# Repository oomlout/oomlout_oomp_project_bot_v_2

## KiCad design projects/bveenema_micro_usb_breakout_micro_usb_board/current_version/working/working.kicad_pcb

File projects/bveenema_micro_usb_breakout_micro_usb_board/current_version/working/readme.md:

# micro_usb_breakout
 
## summary 
* id: bveenema_micro_usb_breakout_micro_usb_board
* user: bveenema
* name: micro_usb_breakout
* board: micro_usb_board
* repo: https://github.com/bveenema/Micro-USB-Breakout
* src_file_repo_kicad_pcb: Obsolete/Rev A/Micro-USB-Board.kicad_pcb
* src_file_repo_kicad_pcb_link: https://github.com/bveenema/Micro-USB-Breakout/tree/master/Obsolete/Rev A/Micro-USB-Board.kicad_pcb

* src_file_repo_sch: Obsolete/Rev A/Micro-USB-Board.sch
* src_file_repo_sch_link: https://github.com/bveenema/Micro-USB-Breakout/tree/master/Obsolete/Rev A/Micro-USB-Board.sch
* full details link: https://github.com/oomlout/oomlout_oomp_project_bot_v_2/tree/main/projects/bveenema_micro_usb_breakout_micro_usb_board/current_version/working

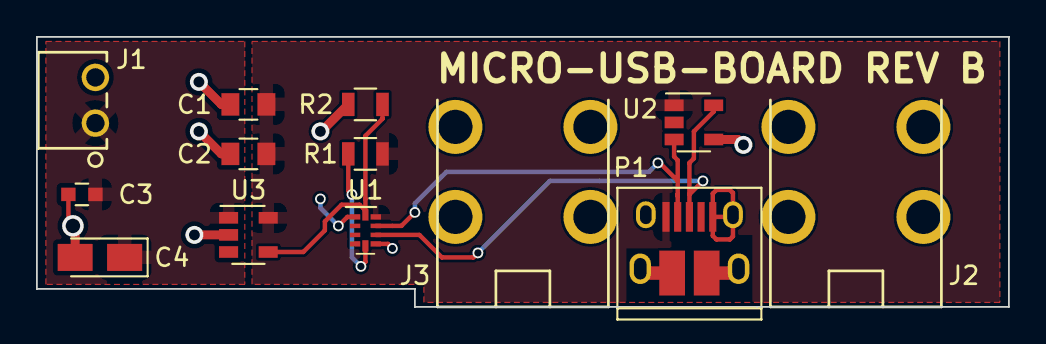
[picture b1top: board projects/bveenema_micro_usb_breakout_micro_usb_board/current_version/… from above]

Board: 2 copper layers, 54.0 x 15.0 mm, 13 parts (0 on the bottom side), 7 nets.

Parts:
C1: 10uF; C_0805
C2: 1uF; C_0805
C3: .1uF; C_0603
C4: 100uF; CP_Tantalum_Case-A_EIA-3216-18_Reflow
J1: 640455-2
J2, J3: Keystone-7790; 7790-ScrewTerm-M3
P1: USB_OTG; USB_Micro-B_10103594-0001LF
R1, R2: 100K; R_0805
U1: BQ24392; Texas_R_PUQFN-N10
U2: TPD2E001; SOT-23-5
U3: AP22811A; SOT-23-5

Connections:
+5V: C3.2, C4.1, J1.1, U3.1
/CHG_DET: R2.1, U1.10, U3.4
/VBUS: C1.2, C2.1, P1.1, R1.1, U1.9, U2.1, U3.5
GND: C1.1, C2.2, C3.1, C4.2, J1.2, P1.5, P1.6, R2.2, U1.6, U2.4, U3.2
unnamed: P1.2, U1.8, U2.3
unnamed: P1.3, U1.7, U2.5
unnamed: R1.2, U1.5

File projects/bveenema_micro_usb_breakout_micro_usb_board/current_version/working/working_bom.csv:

"Id";"Designator";"Footprint";"Quantity";"Designation";"Supplier and ref";
1;"C1";"C_0805";1;"10uF";;;
2;"C2";"C_0805";1;"1uF";;;
3;"C3";"C_0603";1;".1uF";;;
4;"C4";"CP_Tantalum_Case-A_EIA-3216-18_Reflow";1;"100uF";;;
5;"J1";"640455-2";1;"640455-2";;;
6;"P1";"USB_Micro-B_10103594-0001LF";1;"USB_OTG";;;
7;"R1,R2";"R_0805";2;"100K";;;
8;"U1";"Texas_R_PUQFN-N10";1;"BQ24392";;;
9;"U2";"SOT-23-5";1;"TPD2E001";;;
10;"U3";"SOT-23-5";1;"AP22811A";;;
11;"J2,J3";"7790-ScrewTerm-M3";2;"Keystone-7790";;;

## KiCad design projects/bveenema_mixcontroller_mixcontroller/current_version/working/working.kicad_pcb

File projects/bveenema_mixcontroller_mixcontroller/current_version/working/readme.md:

# mixcontroller
 
## summary 
* id: bveenema_mixcontroller_mixcontroller
* user: bveenema
* name: mixcontroller
* board: mixcontroller
* repo: https://github.com/bveenema/MixController
* src_file_repo_kicad_pcb: PCB/MixController.kicad_pcb
* src_file_repo_kicad_pcb_link: https://github.com/bveenema/MixController/tree/master/PCB/MixController.kicad_pcb

* src_file_repo_sch: PCB/MixController.sch
* src_file_repo_sch_link: https://github.com/bveenema/MixController/tree/master/PCB/MixController.sch
* full details link: https://github.com/oomlout/oomlout_oomp_project_bot_v_2/tree/main/projects/bveenema_mixcontroller_mixcontroller/current_version/working

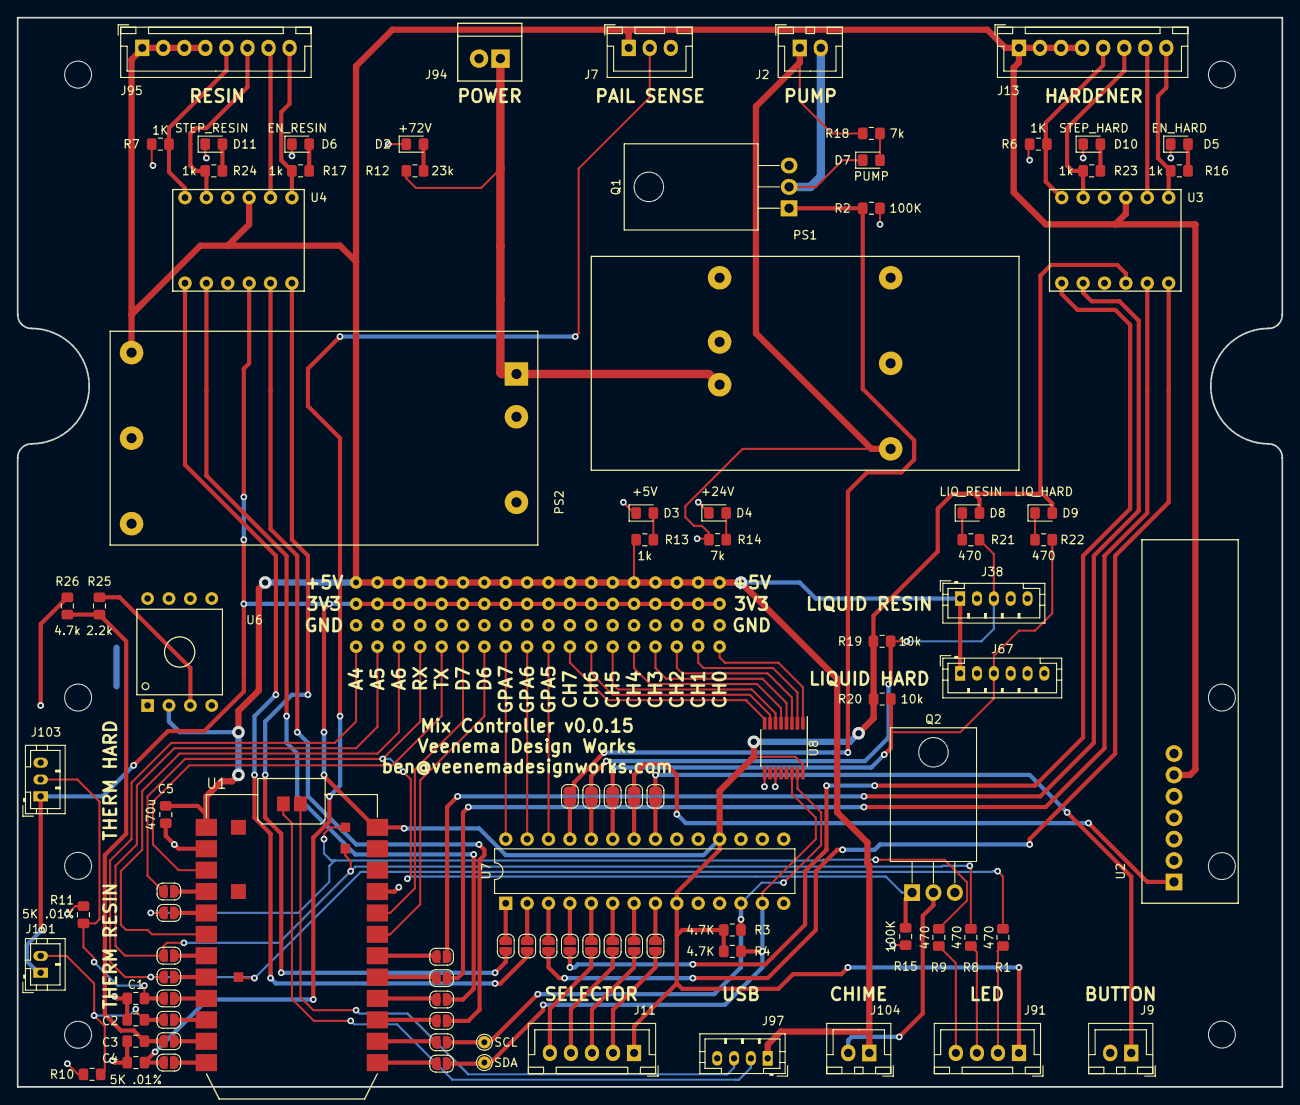
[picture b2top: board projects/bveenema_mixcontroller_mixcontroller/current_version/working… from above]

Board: 2 copper layers, 150.2 x 127.0 mm, 166 parts (0 on the bottom side), 100 nets.

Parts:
C1, C2, C3, C4: 0.1u; C_0805_2012Metric_Pad1.15x1.40mm_HandSolder
C5: 470u; C_0805_2012Metric_Pad1.15x1.40mm_HandSolder
D2: +72V; LED_0805_2012Metric_Pad1.15x1.40mm_HandSolder
D3: +5V; LED_0805_2012Metric_Pad1.15x1.40mm_HandSolder
D4: +24V; LED_0805_2012Metric_Pad1.15x1.40mm_HandSolder
D5: EN_HARD; LED_0805_2012Metric_Pad1.15x1.40mm_HandSolder
D6: EN_RESIN; LED_0805_2012Metric_Pad1.15x1.40mm_HandSolder
D7: PUMP; LED_0805_2012Metric_Pad1.15x1.40mm_HandSolder
D8: LIQ_RESIN; LED_0805_2012Metric_Pad1.15x1.40mm_HandSolder
D9: LIQ_HARD; LED_0805_2012Metric_Pad1.15x1.40mm_HandSolder
D10: STEP_HARD; LED_0805_2012Metric_Pad1.15x1.40mm_HandSolder
D11: STEP_RESIN; LED_0805_2012Metric_Pad1.15x1.40mm_HandSolder
J2, J9, J104: B2B-XH-A(LF)(SN); JST_XH_B02B-XH-A_1x02_P2.50mm_Vertical
J7: B3B-XH-A(LF)(SN); JST_XH_B03B-XH-A_1x03_P2.50mm_Vertical
J11: B5B-XH-A(LF)(SN); JST_XH_B05B-XH-A_1x05_P2.50mm_Vertical
J13, J95: B8B-XH-A(LF)(SN); JST_XH_B08B-XH-A_1x08_P2.50mm_Vertical
J15, J16, J17, J18, J19, J20, J21, J22, J23, J24, J25, J26, J27, J28, J29, J30, J31, J32, J33, J34, J35, J36, J37, J39, J40, J41, J42, J43, J44, J45, J46, J47, J48, J49, J50, J51, J52, J53, J54, J56, J57, J58, J59, J60, J61, J62, J63, J64, J65, J66, J68, J69, J70, J72, J73, J74, J75, J76, J77, J78, J79, J80, J81, J82, J83, J84, J85, J86, J87, J88, J89, J90: ConnectorPoint_THT_D1.5mm_Drill-0.7mm
J38: B5B-PH-K-S(LF)(SN); JST_PH_B5B-PH-K_1x05_P2.00mm_Vertical
J67: B6B-PH-K-S(LF)(SN); JST_PH_B6B-PH-K_1x06_P2.00mm_Vertical
J91: B4B-XH-A(LF)(SN); JST_XH_B04B-XH-A_1x04_P2.50mm_Vertical
J94: 0705430001; Molex-705430001_02x2.54mm_Straight
J97: B4B-PH-K-S(LF)(SN); JST_PH_B4B-PH-K_1x04_P2.00mm_Vertical
J101: B2B-PH-K-S(LF)(SN); JST_PH_B2B-PH-K_1x02_P2.00mm_Vertical
J103: B3B-PH-K-S(LF)(SN); JST_PH_B3B-PH-K_1x03_P2.00mm_Vertical
JP1, JP2, JP3, JP4, JP5, JP6, JP7, JP8, JP9, JP10, JP11, JP12, JP13, JP14, JP15, JP16, JP17, JP18, JP19, JP20, JP21, JP22, JP23, JP24, JP25, JP26, JP27: SolderJumper-2_P1.3mm_Open_RoundedPad1.0x1.5mm
PS1: ERM01H110
PS2: RSDW20H-05; RSDW20_H
Q1, Q2: Q_NMOS_GDS; TO-220-3_Horizontal_TabDown
R1, R8, R9, R21, R22: 470; R_0805_2012Metric_Pad1.15x1.40mm_HandSolder
R2, R15: 100K; R_0805_2012Metric_Pad1.15x1.40mm_HandSolder
R3, R4: 4.7K; R_0805_2012Metric_Pad1.15x1.40mm_HandSolder
R6, R7: 1K; R_0805_2012Metric_Pad1.15x1.40mm_HandSolder
R10, R11: 5K .01%; R_0805_2012Metric_Pad1.15x1.40mm_HandSolder
R12: 23k; R_0805_2012Metric_Pad1.15x1.40mm_HandSolder
R13, R16, R17, R23, R24: 1k; R_0805_2012Metric_Pad1.15x1.40mm_HandSolder
R14, R18: 7k; R_0805_2012Metric_Pad1.15x1.40mm_HandSolder
R19, R20: 10k; R_0805_2012Metric_Pad1.15x1.40mm_HandSolder
R25: 2.2k; R_0805_2012Metric_Pad1.15x1.40mm_HandSolder
R26: 4.7k; R_0805_2012Metric_Pad1.15x1.40mm_HandSolder
TP1: SCL; TestPoint_THTPad_D1.5mm_Drill0.7mm
TP2: SDA; TestPoint_THTPad_D1.5mm_Drill0.7mm
U1: Photon; photon_smd
U2: Adafruit_1096; SimpleRF_Receiver
U3, U4: BOB-12009; BOB-12_W10.16mm
U6: HSCDANN005PGAA5; HoneyWell_DIP_AN
U7: MCP23017_SP; DIP-28_W7.62mm
U8: ADS7830; TSSOP-16_4.4x5mm_P0.65mm

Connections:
+3V3: D8.2, D9.2, J11.1, J20.1, J21.1, J22.1, J23.1, J24.1, J47.1, J48.1, J49.1, J50.1, J51.1, J52.1, J53.1, J54.1, J56.1, J57.1, J58.1, J87.1, J88.1, J91.1, J101.1, J103.1, R3.1, R4.1, R19.1, R20.1, U1.24, U3.4, U4.4, U7.9, U7.18, U8.16
+5V: C5.2, J7.1, J13.1, J13.2, J13.3, J13.4, J15.1, J16.1, J17.1, J18.1, J19.1, J30.1, J31.1, J32.1, J33.1, J34.1, J35.1, J36.1, J37.1, J38.1, J39.1, J40.1, J41.1, J67.1, J89.1, J90.1, J95.1, J95.2, J95.3, J95.4, J97.1, J104.1, PS2.3, R13.1, U1.1, U2.6, U3.9, U4.9, U6.2
+24V: J2.1, PS1.4, R14.2, R18.2
+72V: J94.1, PS1.1, PS2.1, R12.2
/CHIME: J43.1, JP26.1, Q2.1, R15.1
/HARDENER_ENABLE: JP8.1, U3.6
/HARDENER_HLFB: JP9.1, U3.1
/HARDENER_INPUT_DIR: JP19.2, U3.5
/HARDENER_INPUT_STEP: JP18.2, U3.2
/LIQUID_SNS_HARDENER: J67.3, JP16.1, R20.2, R22.1
/LIQUID_SNS_RESIN: J38.3, JP17.1, R19.2, R21.1
/PAIL_SNS: C4.2, J7.2, JP5.1
/PRESS_SNS: C3.2, JP4.1, R25.2, R26.1
/PUMP_EN: JP27.1, Q1.1, R2.1
/RESIN_ENABLE: JP6.1, U4.6
/RESIN_HLFB: JP7.1, U4.1
/RESIN_INPUT_DIR: JP21.2, U4.5
/RESIN_INPUT_STEP: JP20.2, U4.2
/ROTARY_1: J11.2, JP13.1
/ROTARY_2: J11.3, JP12.1
/ROTARY_3: J11.4, JP11.1
/ROTARY_4: J11.5, JP10.1
/SCL: JP22.2, R3.2, TP1.1, U7.12, U8.15
/SDA: JP23.2, R4.2, TP2.1, U7.13, U8.14
/STATUS_LED_B: JP1.1, R9.1, U1.29
/STATUS_LED_G: J45.1, JP2.1, R8.1, U1.28
/STATUS_LED_R: J46.1, JP3.1, R1.1, U1.27
/THERM_HARDENER: C1.2, J103.2, JP24.1, R11.1
/THERM_RESIN: C2.2, J101.2, JP25.1, R10.1
/USB(+): J97.2, U1.31
/USB(-): J97.3, U1.30
/USER_BUTTON: J9.1, JP14.1
/USER_REMOTE: JP15.1, U2.1
GND: C1.1, C2.1, C3.1, C4.1, C5.1, D2.1, D3.1, D4.1, D5.1, D6.1, D10.1, D11.1, J7.3, J9.2, J25.1, J26.1, J27.1, J28.1, J29.1, J38.2, J38.4, J59.1, J60.1, J61.1, J62.1, J63.1, J64.1, J65.1, J66.1, J67.2, J67.4, J68.1, J69.1, J70.1, J85.1, J86.1, J94.2, J97.4, PS1.2, PS1.6, PS2.2, PS2.5, Q1.3, Q2.3, R2.2, R6.1, R7.1, R10.2, R11.2, R15.2, R26.2, U1.2, U1.21, U2.7, U3.3, U3.10, U4.3, U4.10, U6.4, U7.10, U8.9, U8.11
unnamed: D2.2, R12.1
unnamed: D3.2, R13.2
unnamed: D4.2, R14.1
unnamed: D5.2, R16.2
unnamed: D6.2, R17.2
unnamed: D7.1, J2.2, Q1.2
unnamed: D7.2, R18.1
unnamed: D8.1, R21.2
unnamed: D9.1, R22.2
unnamed: D10.2, R23.2
unnamed: D11.2, R24.2
unnamed: J13.5, R6.2, U3.12
unnamed: J13.6, R23.1, U3.11
unnamed: J13.7, U3.8
unnamed: J13.8, R16.1, U3.7
unnamed: J42.1, U1.3
unnamed: J44.1, U1.6
unnamed: J72.1, U7.26
unnamed: J73.1, U7.27
unnamed: J74.1, U7.28
unnamed: J75.1, U8.1
unnamed: J76.1, U8.2
unnamed: J77.1, U8.3
unnamed: J78.1, U8.4
unnamed: J79.1, U8.5
unnamed: J80.1, U8.6
unnamed: J81.1, U8.7
unnamed: J82.1, U8.8
unnamed: J83.1, U1.20
unnamed: J84.1, U1.19
unnamed: J91.2, R1.2
unnamed: J91.3, R8.2
unnamed: J91.4, R9.2
unnamed: J95.5, R7.2, U4.12
unnamed: J95.6, R24.1, U4.11
unnamed: J95.7, U4.8
unnamed: J95.8, R17.1, U4.7
unnamed: J104.2, Q2.2
unnamed: JP1.2, U1.5
unnamed: JP2.2, U1.7
unnamed: JP3.2, U1.8
unnamed: JP4.2, U1.11
unnamed: JP5.2, U1.12
unnamed: JP6.2, U7.1
unnamed: JP7.2, U7.2
unnamed: JP8.2, U7.3
unnamed: JP9.2, U7.4
unnamed: JP10.2, U7.5
unnamed: JP11.2, U7.6
unnamed: JP12.2, U7.7
unnamed: JP13.2, U7.8
unnamed: JP14.2, U7.21
unnamed: JP15.2, U7.22
unnamed: JP16.2, U7.23
unnamed: JP17.2, U7.24
unnamed: JP18.1, U1.18
unnamed: JP19.1, U1.17
unnamed: JP20.1, U1.16
unnamed: JP21.1, U1.15
unnamed: JP22.1, U1.14
unnamed: JP23.1, U1.13
unnamed: JP24.2, U1.9
unnamed: JP25.2, U1.10
unnamed: JP26.2, U1.4
unnamed: JP27.2, U7.25
unnamed: R25.1, U6.3

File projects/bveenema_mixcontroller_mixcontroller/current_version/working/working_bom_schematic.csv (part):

"Source:","C:\gh\oomlout_oomp_project_bot_v_2\projects\bveenema_mixcontroller_mixcontroller\current_version\working\working.kicad_sch"
"Date:","27/09/2023 21:59:41"
"Tool:","Eeschema 7.0.6"
"Generator:","C:/Program Files/KiCad/7.0/bin/scripting/plugins/bom_csv_grouped_by_value_with_fp.py"
"Component Count:","216"
"Ref","Qnty","Value","Cmp name","Footprint","Description","Vendor","DNP"
"C1, C2, C3, C4","4","0.1u","C_Small","Capacitor_SMD:C_0805_2012Metric_Pad1.15x1.40mm_HandSolder","Unpolarized capacitor, small symbol","DigiKey",""
"C5","1","47u","C_Small","Capacitor_SMD:C_0805_2012Metric_Pad1.15x1.40mm_HandSolder","Unpolarized capacitor, small symbol","DigiKey",""
"D1","1","LED_ARGB","LED_ARGB","NoFootprint:NoFootprint","RGB LED, anode/red/green/blue","DigiKey",""
"D2","1","+72V","LED_ALT-Device","LED_SMD:LED_0805_2012Metric_Pad1.15x1.40mm_HandSolder","","DigiKey",""
"D3","1","+5V","LED_ALT-Device","LED_SMD:LED_0805_2012Metric_Pad1.15x1.40mm_HandSolder","","DigiKey",""
"D4","1","+24V","LED_ALT-Device","LED_SMD:LED_0805_2012Metric_Pad1.15x1.40mm_HandSolder","","DigiKey",""
"D5","1","EN_HARD","LED_ALT-Device","LED_SMD:LED_0805_2012Metric_Pad1.15x1.40mm_HandSolder","","DigiKey",""
"D6","1","EN_RESIN","LED_ALT-Device","LED_SMD:LED_0805_2012Metric_Pad1.15x1.40mm_HandSolder","","DigiKey",""
"D7","1","PUMP","LED_ALT-Device","LED_SMD:LED_0805_2012Metric_Pad1.15x1.40mm_HandSolder","","DigiKey",""
"D8","1","LIQ_RESIN","LED_ALT-Device","LED_SMD:LED_0805_2012Metric_Pad1.15x1.40mm_HandSolder","","DigiKey",""
"D9","1","LIQ_HARD","LED_ALT-Device","LED_SMD:LED_0805_2012Metric_Pad1.15x1.40mm_HandSolder","","DigiKey",""
"D10","1","STEP_HARD","LED_ALT-Device","LED_SMD:LED_0805_2012Metric_Pad1.15x1.40mm_HandSolder","","DigiKey",""
"D11","1","STEP_RESIN","LED_ALT-Device","LED_SMD:LED_0805_2012Metric_Pad1.15x1.40mm_HandSolder","","DigiKey",""
"D12","1","LED_RESIN_LIQ","LED_ALT-Device","NoFootprint:NoFootprint","","DigiKey",""
"D13","1","LED_HARD_LIQ","LED_ALT-Device","NoFootprint:NoFootprint","","DigiKey",""
"J1, J5, J6","3","PG7","Conn_01x02_Female-Connector","NoFootprint:NoFootprint","","Amazon",""
"J2, J9, J104","3","B2B-XH-A(LF)(SN)","Conn_01x02_Male-Connector","Connector_JST:JST_XH_B02B-XH-A_1x02_P2.50mm_Vertical","","DigiKey",""
"J3, J10, J105","3","XHP-2","Conn_01x02_Female-Connector","NoFootprint:NoFootprint","","DigiKey",""
"J4, J8","2","XHP-3","Conn_01x03_Female-Connector","NoFootprint:NoFootprint","","DigiKey",""
"J7","1","B3B-XH-A(LF)(SN)","Conn_01x03_Male-Connector","Connector_JST:JST_XH_B03B-XH-A_1x03_P2.50mm_Vertical","","DigiKey",""
"J11","1","B5B-XH-A(LF)(SN)","Conn_01x05_Male-Connector","Connector_JST:JST_XH_B05B-XH-A_1x05_P2.50mm_Vertical","","DigiKey",""
"J12","1","XHP-5","Conn_01x05_Female-Connector","NoFootprint:NoFootprint","","DigiKey",""
"J13, J95","2","B8B-XH-A(LF)(SN)","Conn_01x08_Male-Connector","Connector_JST:JST_XH_B08B-XH-A_1x08_P2.50mm_Vertical","","DigiKey",""
"J14, J96","2","XHP-8","Conn_01x08_Female-Connector","NoFootprint:NoFootprint","","DigiKey",""
"J15, J16, J17, J18, J19, J20, J21, J22, J23, J24, J25, J26, J27, J28, J29, J30, J31, J32, J33, J34, J35, J36, J37, J39, J40, J41, J42, J43, J44, J45, J46, J47, J48, J49, J50, J51, J52, J53, J54, J56, J57, J58, J59, J60, J61, J62, J63, J64, J65, J66, J68, J69, J70, J72, J73, J74, J75, J76, J77, J78, J79, J80, J81, J82, J83, J84, J85, J86, J87, J88, J89, J90","72","~","TestPoint","Local:ConnectorPoint_THT_D1.5mm_Drill-0.7mm","test point","",""
"J38","1","B5B-PH-K-S(LF)(SN)","Conn_01x05_Male-Connector","Connector_JST:JST_PH_B5B-PH-K_1x05_P2.00mm_Vertical","","DigiKey",""
"J55","1","PHR-5","Conn_01x05_Female-Connector","NoFootprint:NoFootprint","","DigiKey",""
"J67","1","B6B-PH-K-S(LF)(SN)","Conn_01x06_Male-Connector","Connector_JST:JST_PH_B6B-PH-K_1x06_P2.00mm_Vertical","","DigiKey",""
"J71","1","PHR-6","Conn_01x06_Female-Connector","NoFootprint:NoFootprint","","DigiKey",""
"J91","1","B4B-XH-A(LF)(SN)","Conn_01x04_Male-Connector","Connector_JST:JST_XH_B04B-XH-A_1x04_P2.50mm_Vertical","","DigiKey",""
"J92","1","XHP-4","Conn_01x04_Female-Connector","NoFootprint:NoFootprint","","DigiKey",""
"J93","1","50-57-9402","Conn_01x02_Female-Connector","NoFootprint:NoFootprint","","DigiKey",""
"J94","1","0705430001","Conn_01x02_Male-Connector","VDW-Connectors:Molex-705430001_02x2.54mm_Straight","","DigiKey",""
"J97","1","B4B-PH-K-S(LF)(SN)","Conn_01x04_Male-Connector","Connector_JST:JST_PH_B4B-PH-K_1x04_P2.00mm_Vertical","","DigiKey",""
"J98","1","PHR-4","Conn_01x04_Female-Connector","NoFootprint:NoFootprint","","DigiKey",""
"J99","1","USB_B","USB_B-Connector","NoFootprint:NoFootprint","","DigiKey",""
"J100","1","PHR-2","Conn_01x02_Female-Connector","NoFootprint:NoFootprint","","DigiKey",""
"J101","1","B2B-PH-K-S(LF)(SN)","Conn_01x02_Male-Connector","Connector_JST:JST_PH_B2B-PH-K_1x02_P2.00mm_Vertical","","DigiKey",""
"J102","1","PHR-3","Conn_01x03_Female-Connector","NoFootprint:NoFootprint","","DigiKey",""
"J103","1","B3B-PH-K-S(LF)(SN)","Conn_01x03_Male-Connector","Connector_JST:JST_PH_B3B-PH-K_1x03_P2.00mm_Vertical","","DigiKey",""
"J106, J108","2","JST SM Male","Conn_01x02_Male-Connector","NoFootprint:NoFootprint","","DigiKey",""
"J107, J109","2","JST SM Female","Conn_01x02_Female-Connector","NoFootprint:NoFootprint","","DigiKey",""
"JP1, JP2, JP3, JP4, JP5, JP6, JP7, JP8, JP9, JP10, JP11, JP12, JP13, JP14, JP15, JP16, JP17, JP18, JP19, JP20, JP21, JP22, JP23, JP24, JP25, JP26, JP27","27","~","Jumper_NC_Small-Device","Jumper:SolderJumper-2_P1.3mm_Open_RoundedPad1.0x1.5mm","","",""
"K1","1","G2R-1A-T DC48","DIPxx-1Axx-11x","NoFootprint:NoFootprint","Standex Meder DIP reed relay, SPST, Closing Contact","DigiKey",""
"KB1","1","Knob","Knob-VDW_Mechanical","NoFootprint:NoFootprint","","DigiKey",""
"LS1","1","Speaker","Speaker","NoFootprint:NoFootprint","Speaker","DigiKey",""
"PS1","1","ERM01H110","ERM01H110-VDW_Modules","VDW-Modules:ERM01H110","","Mouser",""
"PS2","1","RSDW20H-05","RSDW20H-05-VDW_Modules","VDW-Modules:RSDW20_H","","Mouser",""
"Q1, Q2","2","Q_NMOS_GDS","Q_NMOS_GDS","Package_TO_SOT_THT:TO-220-3_Horizontal_TabDown","N-MOSFET transistor, gate/drain/source","DigiKey",""
"R1, R8, R9, R21, R22","5","470","R_Small","Resistor_SMD:R_0805_2012Metric_Pad1.15x1.40mm_HandSolder","Resistor, small symbol","DigiKey",""
"R2, R15","2","100k","R_Small","Resistor_SMD:R_0805_2012Metric_Pad1.15x1.40mm_HandSolder","Resistor, small symbol","DigiKey",""
"R3, R4, R26","3","4.7k","R_Small","Resistor_SMD:R_0805_2012Metric_Pad1.15x1.40mm_HandSolder","Resistor, small symbol","DigiKey",""
"R5","1","2.2k","R","NoFootprint:NoFootprint","Resistor","House",""
"R6, R7, R13, R16, R17, R23, R24","7","1k","R_Small","Resistor_SMD:R_0805_2012Metric_Pad1.15x1.40mm_HandSolder","Resistor, small symbol","DigiKey",""
"R10, R11","2","4.99k .1%","R_Small","Resistor_SMD:R_0805_2012Metric_Pad1.15x1.40mm_HandSolder","Resistor, small symbol","DigiKey",""
"R12","1","22k","R_Small","Resistor_SMD:R_0805_2012Metric_Pad1.15x1.40mm_HandSolder","Resistor, small symbol","DigiKey",""
"R14, R18","2","7.5k","R_Small","Resistor_SMD:R_0805_2012Metric_Pad1.15x1.40mm_HandSolder","Resistor, small symbol","DigiKey",""
"R19, R20","2","10k","R_Small","Resistor_SMD:R_0805_2012Metric_Pad1.15x1.40mm_HandSolder","Resistor, small symbol","DigiKey",""
"R25","1","2.2k","R_Small","Resistor_SMD:R_0805_2012Metric_Pad1.15x1.40mm_HandSolder","Resistor, small symbol","DigiKey",""
"R27, R28","2","470","R_Small","NoFootprint:NoFootprint","Resistor, small symbol","House",""
"R29","1","22k","R","NoFootprint:NoFootprint","Resistor","House",""
"SP1, SP8, SP9","3","LED_HOLDER_5MM","LED_HOLDER_5MM-VDW_Mechanical","NoFootprint:NoFootprint","","DigiKey",""
"SP2, SP3, SP4, SP5, SP6, SP7","6","PG7","PG7-VDW_Mechanical","NoFootprint:NoFootprint","","Amazon",""
"SW1","1","Rotary_Selector_Switch","Rotary_Selector_Switch-VDW_Modules","NoFootprint:NoFootprint","","DigiKey",""
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
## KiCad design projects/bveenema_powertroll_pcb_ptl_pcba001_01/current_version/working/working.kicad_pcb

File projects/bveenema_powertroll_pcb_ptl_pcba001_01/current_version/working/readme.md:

# powertroll_pcb
 
## summary 
* id: bveenema_powertroll_pcb_ptl_pcba001_01
* user: bveenema
* name: powertroll_pcb
* board: ptl_pcba001_01
* repo: https://github.com/bveenema/powertroll-pcb
* src_file_repo_kicad_pcb: PTL-PCBA001-01.kicad_pcb
* src_file_repo_kicad_pcb_link: https://github.com/bveenema/powertroll-pcb/tree/master/PTL-PCBA001-01.kicad_pcb

* src_file_repo_sch: PTL-PCBA001-01.sch
* src_file_repo_sch_link: https://github.com/bveenema/powertroll-pcb/tree/master/PTL-PCBA001-01.sch
* full details link: https://github.com/oomlout/oomlout_oomp_project_bot_v_2/tree/main/projects/bveenema_powertroll_pcb_ptl_pcba001_01/current_version/working

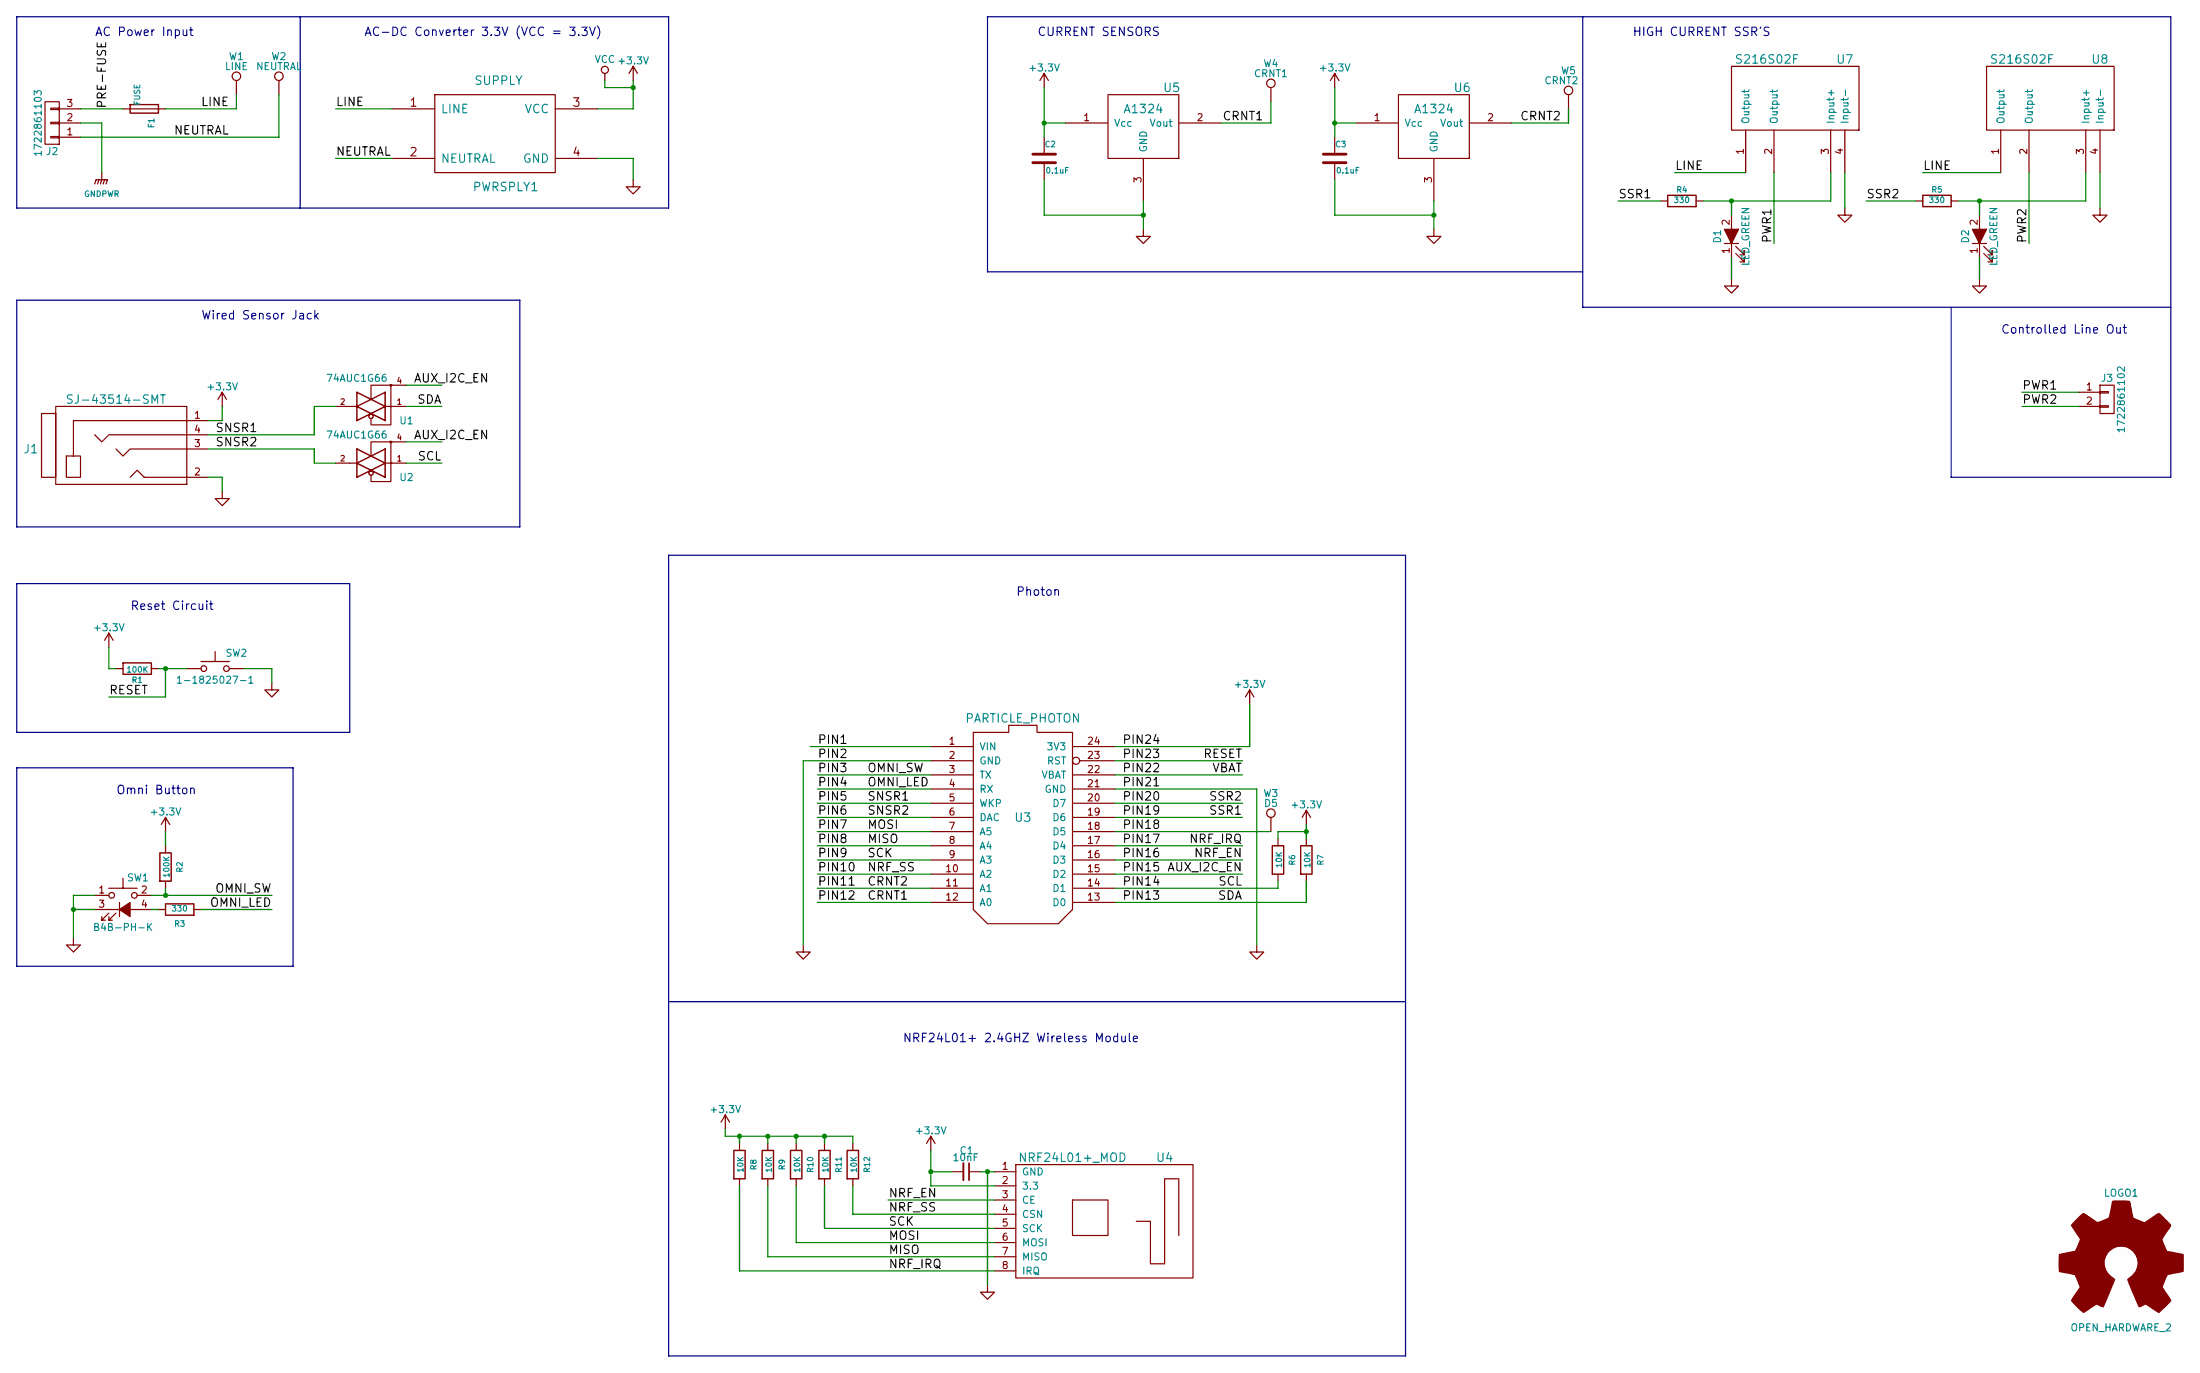
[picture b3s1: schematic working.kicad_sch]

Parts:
C1: 10nF; C_0805; Part Number CL21B103KBANNNC
C2, C3: 0.1uF; C_0805_HandSoldering
D1, D2: LED_GREEN; LED_0805
F1: FUSE; Fuseholder5x20_horiz_open_inline_Type-I
J1: SJ-43514-SMT
J2: 1722861103; Molex_UltraFit-1722861103_3x3.50mm_Straight
J3: 1722861102; Molex_UltraFit-1722861102_2x3.50mm_Straight
LOGO1: OPEN_HARDWARE_2; OSHW-Symbol_6.7x6mm_SilkScreen
PWRSPLY1: SUPPLY; PowerSupply
R1, R2: 100K; R_0805_HandSoldering
R3, R4, R5: 330; R_0805_HandSoldering
R6, R7, R8, R9, R10, R11, R12: 10K; R_0805_HandSoldering
SW1: B4B-PH-K; JST_PH_B4B-PH-K_04x2.00mm_Straight
SW2: 1-1825027-1; SW_Tactile_SPST_Angled
U1, U2: 74AUC1G66; SOT-23-5
U3: PARTICLE_PHOTON; photon
U4: NRF24L01+_MOD; NRF24L01
U5, U6: A1324; SOT-23
U7, U8: S216S02F; S216S02
W1: LINE; Measurement_Point_Round-TH_Small
W2: NEUTRAL; Measurement_Point_Round-TH_Small
W3: D5; Measurement_Point_Round-TH_Small
W4: CRNT1; Measurement_Point_Round-SMD-Pad_Small
W5: CRNT2; Measurement_Point_Round-SMD-Pad_Small

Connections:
+3V3: C1.2, C2.1, C3.1, J1.1, PWRSPLY1.3 (VCC), R1.2, R2.1, R6.1, R7.1, R8.1, R9.1, R10.1, R11.1, R12.1, U1.5 (VCC), U2.5 (VCC), U3.24 (3V3), U4.2 (3.3), U5.1 (Vcc), U6.1 (Vcc)
/AUX_I2C_EN: U1.4, U2.4, U3.15 (D2)
/CRNT1: U3.12 (A0), U5.2 (Vout), W4.1
/CRNT2: U3.11 (A1), U6.2 (Vout), W5.1
/LINE: F1.1, PWRSPLY1.1 (LINE), U7.1 (Output), U8.1 (Output), W1.1
/MISO: R9.2, U3.8 (A4), U4.7 (MISO)
/MOSI: R10.2, U3.7 (A5), U4.6 (MOSI)
/NEUTRAL: J2.1, PWRSPLY1.2 (NEUTRAL), W2.1
/NRF_EN: U3.16 (D3), U4.3 (CE)
/NRF_IRQ: R8.2, U3.17 (D4), U4.8 (IRQ)
/NRF_SS: R12.2, U3.10 (A2), U4.4 (CSN)
/OMNI_LED: R3.2, U3.4 (RX)
/OMNI_SW: R2.2, SW1.2, U3.3 (TX)
/PIN1: U3.1 (VIN)
/PIN5: J1.4, U1.2, U3.5 (WKP)
/PIN6: J1.3, U2.2, U3.6 (DAC)
/PIN9: R11.2, U3.9 (A3), U4.5 (SCK)
/PIN13: R7.2, U1.1, U3.13 (D0)
/PIN14: R6.2, U2.1, U3.14 (D1)
/PIN18: U3.18 (D5), W3.1
/PIN19: R4.1, U3.19 (D6)
/PIN20: R5.1, U3.20 (D7)
/PIN22: U3.22 (VBAT)
/PIN23: R1.1, SW2.1, U3.23 (RST)
/PRE-FUSE: F1.2, J2.3
/PWR1: J3.1, U7.2 (Output)
/PWR2: J3.2, U8.2 (Output)
GND: C1.1, C2.2, C3.2, D1.1 (K), D2.1 (K), J1.2, PWRSPLY1.4 (GND), SW1.1, SW1.3 (K), SW2.2, U1.3 (GND), U2.3 (GND), U3.2 (GND), U3.21 (GND), U4.1 (GND), U5.3 (GND), U6.3 (GND), U7.4 (Input-), U8.4 (Input-)
GNDPWR: J2.2
unnamed: D1.2 (A), R4.2, U7.3 (Input+)
unnamed: D2.2 (A), R5.2, U8.3 (Input+)
unnamed: R3.1, SW1.4 (A)

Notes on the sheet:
Wired Sensor Jack
HIGH CURRENT SSR'S
AC Power Input
Photon
Omni Button
AC-DC Converter 3.3V (VCC = 3.3V)
Controlled Line Out
Reset Circuit
CURRENT SENSORS
NRF24L01+ 2.4GHZ Wireless Module

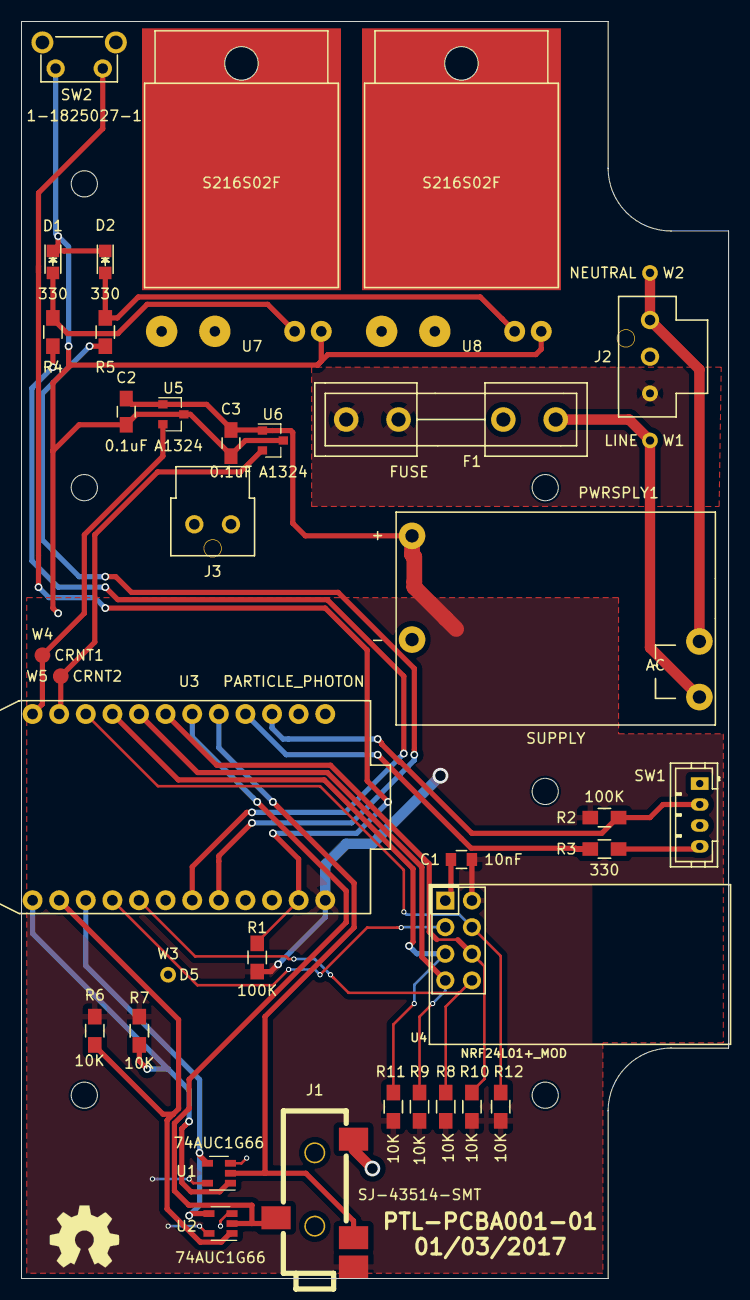
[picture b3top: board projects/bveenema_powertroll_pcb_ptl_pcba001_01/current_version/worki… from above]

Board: 2 copper layers, 67.5 x 120.0 mm, 38 parts (0 on the bottom side), 29 nets.

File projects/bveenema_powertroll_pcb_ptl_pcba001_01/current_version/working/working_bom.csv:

"Id";"Designator";"Footprint";"Quantity";"Designation";"Supplier and ref";
1;"C1";"C_0805";1;"10nF";;;
2;"C2,C3";"C_0805_HandSoldering";2;"0.1uF";;;
3;"D1,D2";"LED_0805";2;"LED_GREEN";;;
4;"F1";"Fuseholder5x20_horiz_open_inline_Type-I";1;"FUSE";;;
5;"J1";"SJ-43514-SMT";1;"SJ-43514-SMT";;;
6;"J2";"Molex_UltraFit-1722861103_3x3.50mm_Straight";1;"CONN_01X03";;;
7;"J3";"Molex_UltraFit-1722861102_2x3.50mm_Straight";1;"CONN_01X02";;;
8;"PWRSPLY1";"PowerSupply";1;"SUPPLY";;;
9;"R1,R2";"R_0805_HandSoldering";2;"100K";;;
10;"R3,R4,R5";"R_0805_HandSoldering";3;"330";;;
11;"SW1";"JST_PH_B4B-PH-K_04x2.00mm_Straight";1;"SW_Push_LED";;;
12;"SW2";"SW_Tactile_SPST_Angled";1;"1-1825027-1";;;
13;"U1,U2";"SOT-23-5";2;"74AUC1G66";;;
14;"U3";"photon";1;"PARTICLE_PHOTON";;;
15;"U4";"NRF24L01";1;"NRF24L01+_MOD";;;
16;"U5,U6";"SOT-23";2;"A1324";;;
17;"U7,U8";"S216S02";2;"S216S02F";;;
18;"REF**,REF**,REF**,REF**,REF**,REF**";"MountingHole_2.5x4mm";6;"MountingHole_2.5x4mm";;;
19;"R6,R7,R8,R9,R10,R11,R12";"R_0805_HandSoldering";7;"10K";;;

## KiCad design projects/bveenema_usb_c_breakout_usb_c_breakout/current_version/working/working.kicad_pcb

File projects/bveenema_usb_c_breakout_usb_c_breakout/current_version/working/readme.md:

# usb_c_breakout
 
## summary 
* id: bveenema_usb_c_breakout_usb_c_breakout
* user: bveenema
* name: usb_c_breakout
* board: usb_c_breakout
* repo: https://github.com/bveenema/USB-C_Breakout
* src_file_repo_kicad_pcb: USB-C_Breakout.kicad_pcb
* src_file_repo_kicad_pcb_link: https://github.com/bveenema/USB-C_Breakout/tree/master/USB-C_Breakout.kicad_pcb

* src_file_repo_sch: USB-C_Breakout.sch
* src_file_repo_sch_link: https://github.com/bveenema/USB-C_Breakout/tree/master/USB-C_Breakout.sch
* full details link: https://github.com/oomlout/oomlout_oomp_project_bot_v_2/tree/main/projects/bveenema_usb_c_breakout_usb_c_breakout/current_version/working

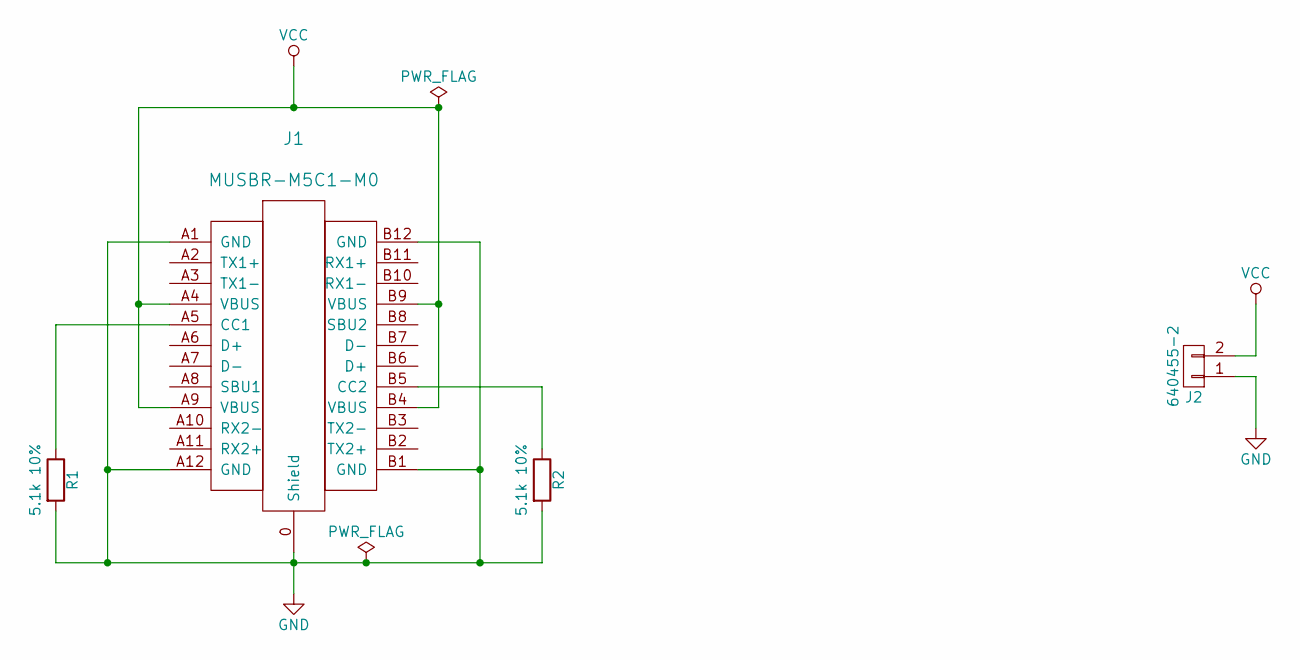
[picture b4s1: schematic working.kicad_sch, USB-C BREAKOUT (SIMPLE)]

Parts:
J1: MUSBR-M5C1-M0; MUSBR-M5C1-X0
J2: 640455-2
R1, R2: 5.1k 10%; R_0805

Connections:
GND: J1.0 (Shield), J1.A1 (GND), J1.A12 (GND), J1.B1 (GND), J1.B12 (GND), J1.G1 (GND), J1.G2 (GND), J1.G3 (GND), J1.G4 (GND), J1.G5 (GND), J1.G6 (GND), J2.1, R1.2, R2.2
unnamed: J1.A5 (CC1), R1.1
unnamed: J1.B5 (CC2), R2.1
VCC: J1.A4 (VBUS), J1.A9 (VBUS), J1.B4 (VBUS), J1.B9 (VBUS), J2.2

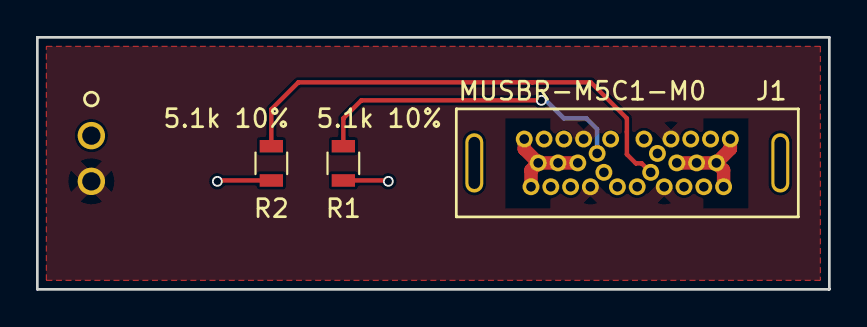
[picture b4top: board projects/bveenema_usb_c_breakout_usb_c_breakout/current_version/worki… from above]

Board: 2 copper layers, 44.0 x 14.0 mm, 4 parts (1 on the bottom side), 4 nets.

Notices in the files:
parts and their libraries:
Copyright 2016 Accelerated Designs. All rights reserved.
